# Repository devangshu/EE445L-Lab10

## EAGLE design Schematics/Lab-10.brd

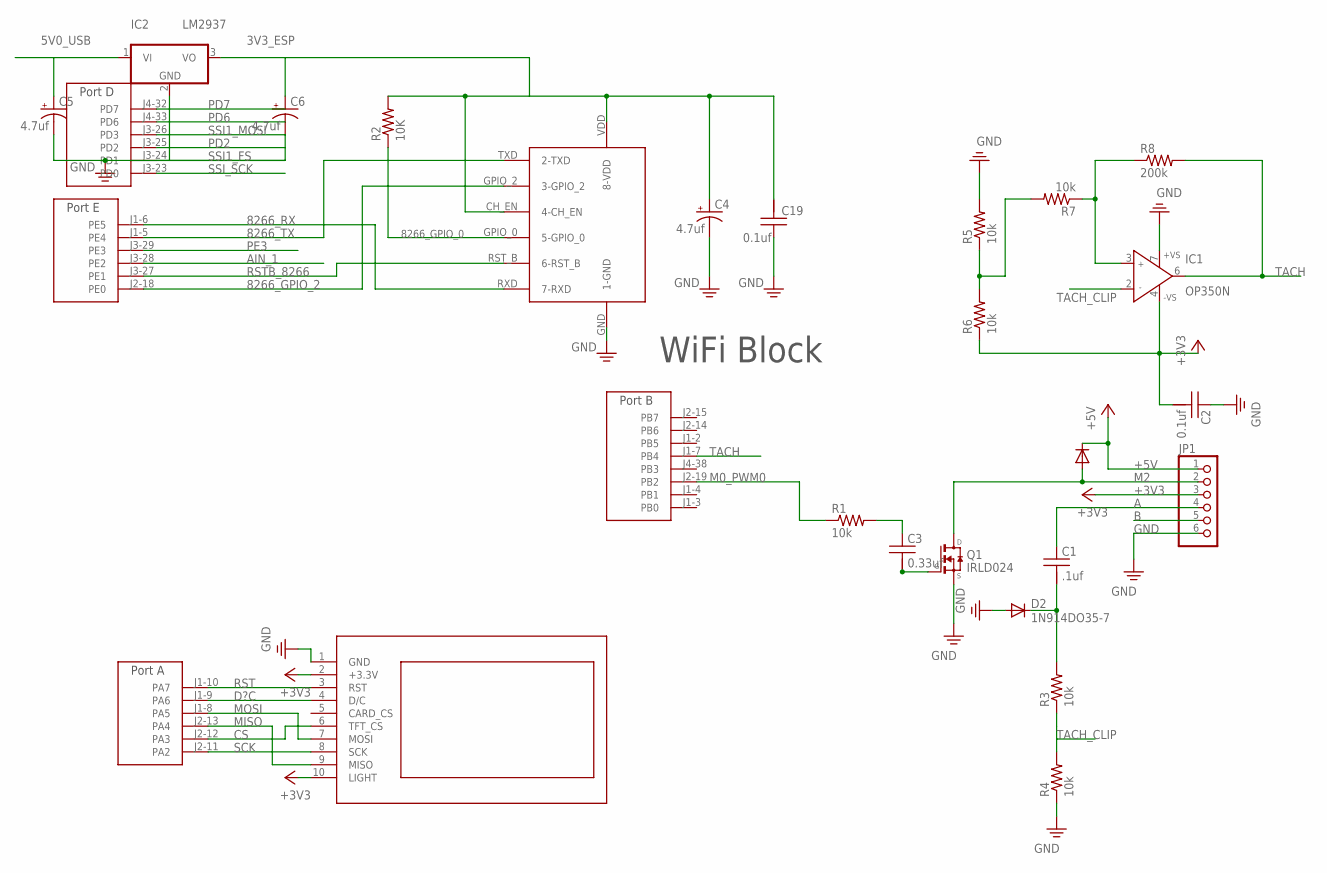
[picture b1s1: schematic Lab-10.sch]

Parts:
C1: .1uf; CAP100MIL
C2: 0.1uf; CAP100MIL
C3: 0.33uf; CAP100MIL
C4, C5, C6: 4.7uf; CAP200MILPOLARIZED
C19: 0.1uf; CAP200MIL
D1, D2: 1N914DO35-7; DO35-7
IC1: OP350N; DIL08
IC2: LM2937; TO263-3
JP1: PINHD-1X6; 1X06
Q1: IRLD024
R1, R5, R6, R7: 10k; RES200MIL
R2: 10K; RES300MIL
R3, R4: 10k; RES300MIL
R8: 200k; RES200MIL
U$1, U$4, U$5: TM4C_BP; TM4C_BOOSTER_PACK
U$2: ST7735
U$3: ESP_8266; ESP8266

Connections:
3V3_ESP: C4.+, C6.+, C19.2, IC2.3 (VO), R2.2, U$3.CH_EN (4-CH_EN), U$3.VDD (8-VDD)
5V0_USB: C5.+, IC2.1 (VI)
8266_GPIO_0: R2.1, U$3.GPIO_0 (5-GPIO_0)
8266_GPIO_2: U$3.GPIO_2 (3-GPIO_2), U$4.J2-18 (PE0)
8266_RX: U$3.RXD (7-RXD), U$4.J1-6 (PE5)
8266_TX: U$3.TXD (2-TXD), U$4.J1-5 (PE4)
+3V3: C2.2, IC1.4 (-VS), JP1.3, R6.1, U$2.2 (+3.3V), U$2.10 (LIGHT)
+5V: D1.C, JP1.1
A: C1.1, JP1.4
AIN_1: U$4.J3-28 (PE2)
B: JP1.5
CS: U$1.J2-12 (PA3), U$2.6 (TFT_CS)
D?C: U$1.J1-9 (PA6), U$2.4 (D/C)
GND: C2.1, C4.-, C5.-, C6.-, C19.1, D2.A, IC1.7 (+VS), IC2.2 (GND), JP1.6, Q1.P$4 (S), R4.1, R5.2, U$2.1 (GND), U$3.GND (1-GND)
M0_PWM0: R1.1, U$1.J2-19 (PB2)
M2: D1.A, JP1.2, Q1.P$1 (D)
MISO: U$1.J2-13 (PA4), U$2.9 (MISO)
MOSI: U$1.J1-8 (PA5), U$2.7 (MOSI)
unnamed: C3.1, R1.2
unnamed: C1.2, D2.C, R3.2
unnamed: C3.2, Q1.P$3 (G)
unnamed: R5.1, R6.2, R7.2
unnamed: IC1.3 (IN+), R7.1, R8.1
PD2: U$5.J3-25 (PD2)
PD6: U$5.J4-33 (PD6)
PD7: U$5.J4-32 (PD7)
PE3: U$4.J3-29 (PE3)
RST: U$1.J1-10 (PA7), U$2.3 (RST)
RSTB_8266: U$3.RST_B (6-RST_B), U$4.J3-27 (PE1)
SCK: U$1.J2-11 (PA2), U$2.8 (SCK)
SSI1_FS: U$5.J3-24 (PD1)
SSI1_MOSI: U$5.J3-26 (PD3)
SSI_SCK: U$5.J3-23 (PD0)
TACH: IC1.6 (OUT), R8.2, U$1.J1-7 (PB4)
TACH_CLIP: IC1.2 (IN-), R3.1, R4.2

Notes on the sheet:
WiFi Block

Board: 2 copper layers, 26 parts (0 on the bottom side), 26 nets, no tracks yet.

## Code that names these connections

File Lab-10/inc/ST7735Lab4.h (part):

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// ST7735
// Backlight (pin 10) connected to +3.3 V
// MISO (pin 9) unconnected
// SCK (pin 8) connected to PA2 (SSI0Clk)
// MOSI (pin 7) connected to PA5 (SSI0Tx)
// TFT_CS (pin 6) connected to PA3 (SSI0Fss)
// CARD_CS (pin 5) unconnected
// Data/Command (pin 4) connected to PA6 (GPIO), high for data, low for command
// RESET (pin 3) connected to PA7 (GPIO)
// VCC (pin 2) connected to +3.3 V
// Gnd (pin 1) connected to ground

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// Silkscreen Label (SDC side up; LCD side down) - Connection
// VCC  - +3.3 V
// GND  - Ground
// !SCL - PA2 Sclk SPI clock from microcontroller to TFT or SDC
// !SDA - PA5 MOSI SPI data from microcontroller to TFT or SDC
// DC   - PA6 TFT data/command
// RES  - PA7 TFT reset
// CS   - PA3 TFT_CS, active low to enable TFT
// *CS  - (NC) SDC_CS, active low to enable SDC
// MISO - (NC) MISO SPI data from SDC to microcontroller
// SDA  � (NC) I2C data for ADXL345 accelerometer
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// Silkscreen Label (SDC side up; LCD side down) - Connection
// VCC  - +3.3 V
// GND  - Ground
// !SCL - PA2 Sclk SPI clock from microcontroller to TFT or SDC
// !SDA - PA5 MOSI SPI data from microcontroller to TFT or SDC
// DC   - PA6 TFT data/command
// RES  - PA7 TFT reset
// CS   - PA3 TFT_CS, active low to enable TFT
// *CS  - (NC) SDC_CS, active low to enable SDC
// MISO - (NC) MISO SPI data from SDC to microcontroller
// X� (NC) analog input X-axis from ADXL335 accelerometer
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// MOSI   (pin 13) SDC, MOSI
// MISO   (pin 12) SDC, MISO
// SCK    (pin 11) SDC, serial clock
// CS     (pin 10) TFT, PA3 (SSI0Fss)
// SCL    (pin 9)  TFT, SCK  PA2 (SSI0Clk)
// SDA    (pin 8)  TFT, MOSI PA5 (SSI0Tx)
// A0     (pin 7)  TFT, Data/Command PA6 (GPIO), high for data, low for command
// RESET  (pin 6)  TFT, to PA7 (GPIO)
// NC     (pins 3,4,5) not connected
// VCC    (pin 2)  connected to +3.3 V
// GND    (pin 1)  connected to ground
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
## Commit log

2021-11-11 Added starter schematic files
2021-11-11 Hooked up Motor interface
2021-11-11 Tachometer circuit complete (but messy)
2021-11-11 Added basic headers
2021-11-11 add switch and esp drivers
2021-11-12 Modified changes after prep checkout
2021-11-16 Motor Spins
2021-11-16 working on Blynk side real quick
2021-11-16 rps measurement with tachometer
2021-11-16 blynk should be set up (rudimentary), gonna set some stuff for LCD
2021-11-16 start working on pi loop
2021-11-16 working pi looop
2021-11-16 Set up code to plot the two lines
    Still need to normalize the y values properly to fit in the bounds of
    the screen
2021-11-16 Normalized y plotting values
2021-11-16 Trying to make LCD work
2021-11-16 working lcd
2021-11-19 added some comments, each variable has some kind of unit / explanation for why
2021-11-19 Added LCD interface to the schematic
2021-11-19 Added wifi block
2021-11-20 Software method to check elapsed time
2021-11-20 Initialized SysTick

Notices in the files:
Lab-10/inc/ST7735Lab4.h:
MIT license, all text above must be included in any redistribution
"Embedded Systems: Introduction to ARM Cortex M Microcontrollers",
ISBN: 978-1469998749, Jonathan Valvano, copyright (c) 2020
Copyright 2020 by Jonathan W. Valvano, valvano@mail.utexas.edu
